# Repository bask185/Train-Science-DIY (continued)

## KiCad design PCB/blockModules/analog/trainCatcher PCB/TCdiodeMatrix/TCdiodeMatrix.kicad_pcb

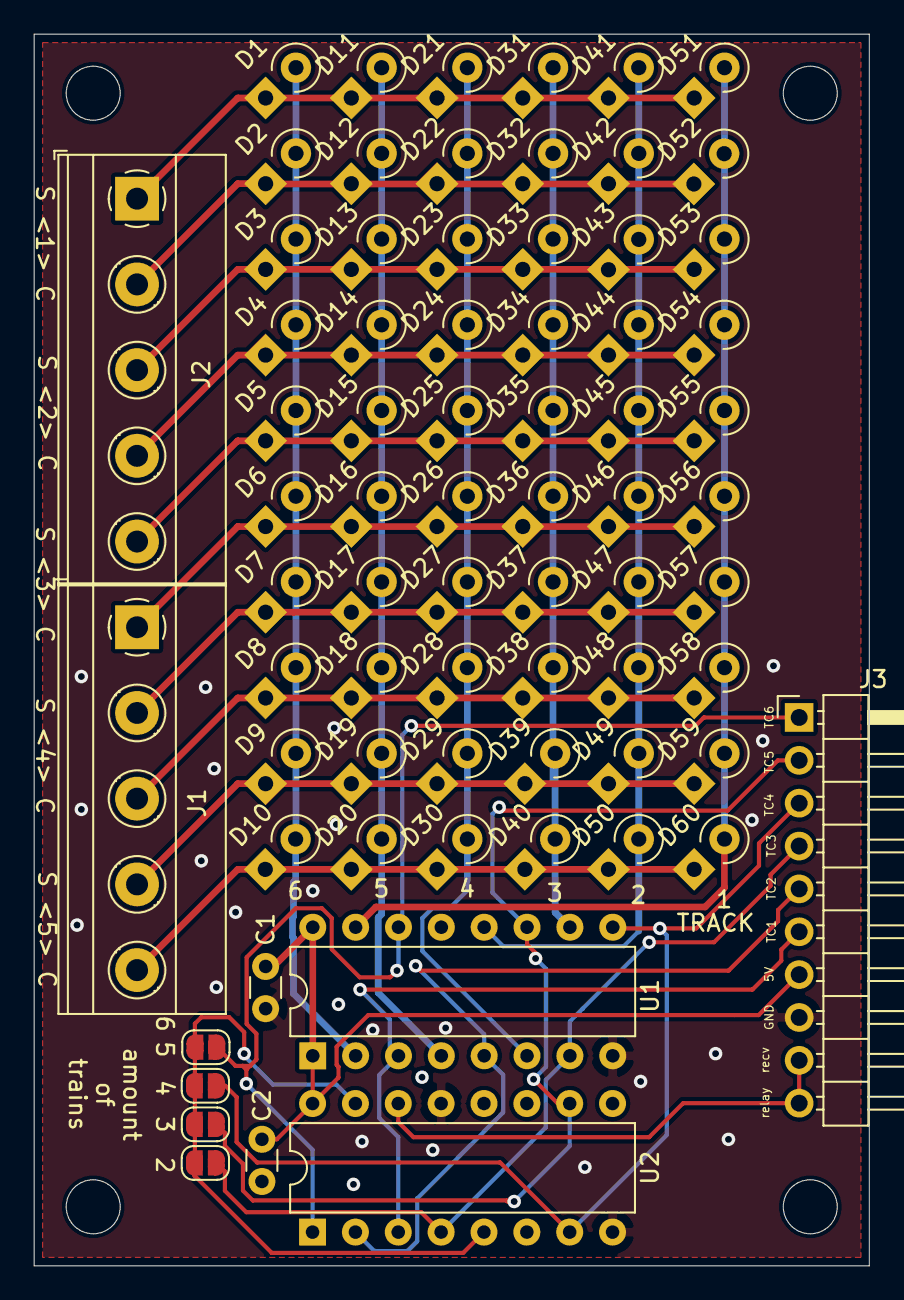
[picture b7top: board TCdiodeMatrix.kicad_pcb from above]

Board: 2 copper layers, 49.5 x 73.0 mm, 71 parts (0 on the bottom side), 26 nets.

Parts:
C1, C2: C; C_Disc_D3.0mm_W1.6mm_P2.50mm
D1, D2, D3, D4, D5, D6, D7, D8, D9, D10, D11, D12, D13, D14, D15, D16, D17, D18, D19, D20, D21, D22, D23, D24, D25, D26, D27, D28, D29, D30, D31, D32, D33, D34, D35, D36, D37, D38, D39, D40, D41, D42, D43, D44, D45, D46, D47, D48, D49, D50, D51, D52, D53, D54, D55, D56, D57, D58, D59, D60: D; D_A-405_P2.54mm_Vertical_KathodeUp
J1, J2: points; TerminalBlock_Phoenix_MKDS-1,5-5-5.08_1x05_P5.08mm_Horizont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
J3: train catchers; PinHeader_1x10_P2.54mm_Horizontal
JP1, JP2, JP3, JP4: ju; SolderJumper-2_P1.3mm_Open_RoundedPad1.0x1.5mm
U1: 4009; DIP-16_W7.62mm
U2: 4017; DIP-16_W7.62mm

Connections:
+5V: C1.1, C2.1, J3.7, U1.1, U1.16, U2.16
/TC1: D51.2, D52.2, D53.2, D54.2, D55.2, D56.2, D57.2, D58.2, D59.2, D60.2, U1.15
/TC2: D41.2, D42.2, D43.2, D44.2, D45.2, D46.2, D47.2, D48.2, D49.2, D50.2, U1.12
/TC3: D31.2, D32.2, D33.2, D34.2, D35.2, D36.2, D37.2, D38.2, D39.2, D40.2, U1.10
/TC4: D21.2, D22.2, D23.2, D24.2, D25.2, D26.2, D27.2, D28.2, D29.2, D30.2, U1.6
/TC5: D11.2, D12.2, D13.2, D14.2, D15.2, D16.2, D17.2, D18.2, D19.2, D20.2, U1.4
/TC6: D1.2, D2.2, D3.2, D4.2, D5.2, D6.2, D7.2, D8.2, D9.2, D10.2, U1.2
/TC_out1: J3.6, U1.3, U2.3
/TC_out2: J3.5, U1.5, U2.2
/TC_out3: J3.4, JP1.1, U1.7, U2.4
/TC_out4: J3.3, JP2.1, U1.9, U2.7
/TC_out5: J3.2, JP3.1, U1.11, U2.10
/TC_out6: J3.1, JP4.1, U1.14, U2.1
/recv: J3.9, J3.10, U2.14
/reset: JP1.2, JP2.2, JP3.2, JP4.2, U2.5, U2.15
GND: C1.2, C2.2, J3.8, U1.8, U2.8, U2.13
unnamed: D1.1, D11.1, D21.1, D31.1, D41.1, D51.1, J2.1
unnamed: D10.1, D20.1, D30.1, D40.1, D50.1, D60.1, J1.5
unnamed: D2.1, D12.1, D22.1, D32.1, D42.1, D52.1, J2.2
unnamed: D3.1, D13.1, D23.1, D33.1, D43.1, D53.1, J2.3
unnamed: D4.1, D14.1, D24.1, D34.1, D44.1, D54.1, J2.4
unnamed: D5.1, D15.1, D25.1, D35.1, D45.1, D55.1, J2.5
unnamed: D6.1, D16.1, D26.1, D36.1, D46.1, D56.1, J1.1
unnamed: D7.1, D17.1, D27.1, D37.1, D47.1, D57.1, J1.2
unnamed: D8.1, D18.1, D28.1, D38.1, D48.1, D58.1, J1.3
unnamed: D9.1, D19.1, D29.1, D39.1, D49.1, D59.1, J1.4

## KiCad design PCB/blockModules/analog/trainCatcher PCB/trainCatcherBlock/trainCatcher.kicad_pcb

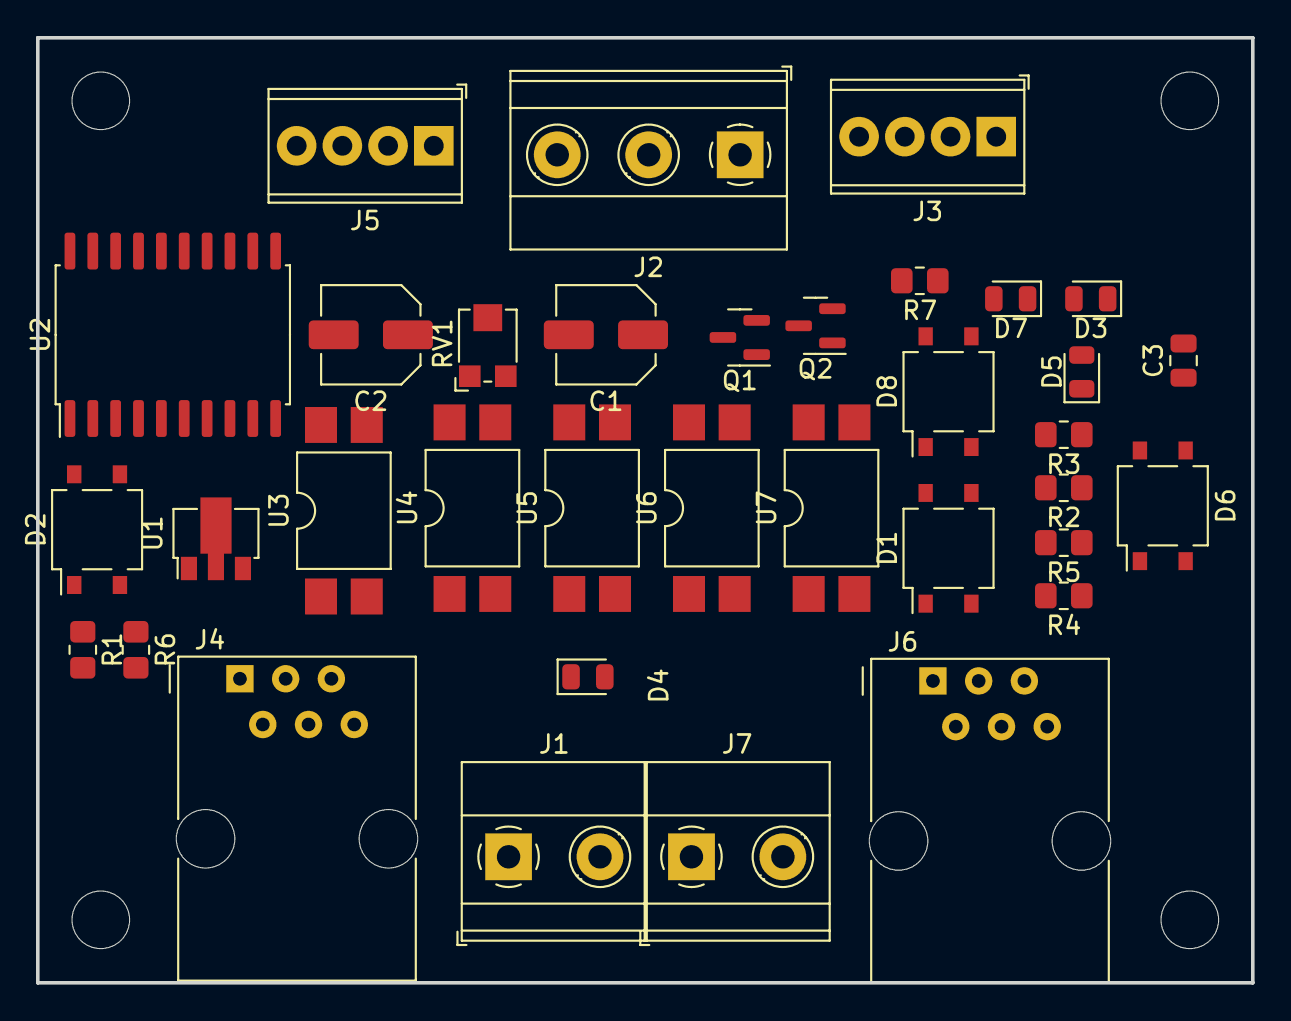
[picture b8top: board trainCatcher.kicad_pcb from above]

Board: 2 copper layers, 67.5 x 52.5 mm, 35 parts (0 on the bottom side), 32 nets, no tracks yet.

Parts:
C1, C2: 33uF; C_Elec_5x5.4
C3: 100nF; C_0805_2012Metric
D1: D_Bridge; TO-269AA
D2, D6, D8: D_Bridge_+-AA; TO-269AA
D3, D7: D; D_0805_2012Metric
D4, D5: D_Schottky; D_0805_2012Metric
J1, J7: Screw_Terminal_01x02; TerminalBlock_Phoenix_MKDS-1,5-2-5.08_1x02_P5.08mm_Horizont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
J2: Screw_Terminal_01x03; TerminalBlock_Phoenix_MKDS-1,5-3-5.08_1x03_P5.08mm_Horizont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
J3, J5: signal; TerminalBlock_Phoenix_MPT-0,5-4-2.54_1x04_P2.54mm_Horizontal
J4, J6: RJ12; RJ12_Amphenol_54601
Q1, Q2: IRLML2060; SOT-23
R1, R5: 100k; R_0805_2012Metric_Pad1.20x1.40mm_HandSolder
R2, R3: 470R; R_0805_2012Metric_Pad1.20x1.40mm_HandSolder
R4, R6: 33R; R_0805_2012Metric_Pad1.20x1.40mm_HandSolder
R7: 1k5; R_0805_2012Metric_Pad1.20x1.40mm_HandSolder
RV1: R_POT; Potentiometer_Bourns_TC33X_Vertical
U1: L78L05_SOT89; SOT-89-3
U2: ATtiny2313-20S; SOIC-20W_7.5x12.8mm_P1.27mm
U3, U5: EL814; SMDIP-4_W9.53mm
U4, U6, U7: EL817; SMDIP-4_W9.53mm

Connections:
+5V: C2.1, C3.2, RV1.3, U1.1 (OUT), U2.20 (VCC)
+12V: J3.1, J5.1
/A: U2.16 (PB4), U3.4
/B: U2.17 (PB5), U5.4
/PWM: R2.1, R3.1, U2.14 (PB2)
/breakSpeed: RV1.2, U2.15 (PB3)
/buffer: D8.3, J2.2
/dir: U2.18 (PB6), U4.4
/downline: J4.3, J6.3, U2.13 (PB1)
/green_up: J3.3, J5.3, U2.3 (PD1), U2.8 (PD4)
/leftTrack: D1.3, J1.2, J4.6, J6.6, R5.1, U4.1, U7.4
/red_up: J3.2, J5.2, U2.6 (PD2), U2.9 (PD5)
/rightTrack: D1.4, D5.2 (A), J1.1, J4.5, J6.5, Q2.2 (S), R1.2, U6.4
/switch_go: J7.2, U2.19 (PB7)
/track_A: D2.3, J2.1, R4.2
/track_B: D6.3, J2.3, R6.2
/upline: J4.4, J6.4, U2.12 (PB0)
/yellow_up: J3.4, J5.4, U2.2 (PD0), U2.7 (PD3)
GND: C1.2, C2.2, C3.1, D1.2 (-), J4.2, J6.2, J7.1, R7.2, RV1.1, U1.2 (GND), U2.10 (GND), U3.3, U4.3, U6.2, U7.2
unnamed: C1.1, D1.1 (+), U1.3 (IN)
unnamed: D2.1 (+), D2.2 (-)
unnamed: D2.4, D3.1 (K), D4.2 (A), D6.4, D7.1 (K), D8.4, Q1.2 (S), U3.1, U5.1, U5.3
unnamed: D3.2 (A), R4.1, U3.2
unnamed: D4.1 (K), D5.1 (K), Q1.3 (D), Q2.3 (D)
unnamed: D6.1 (+), D6.2 (-)
unnamed: D7.2 (A), R6.1, U5.2
unnamed: D8.1 (+), D8.2 (-)
unnamed: Q1.1 (G), R5.2, U6.3
unnamed: Q2.1 (G), R1.1, U7.3
unnamed: R2.2, U6.1
unnamed: R3.2, U7.1
unnamed: R7.1, U4.2
